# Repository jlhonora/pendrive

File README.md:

Build your own pendrive
=======================

This repo contains all the necessary material to build your own open-source pendrive, including the software source code, the design files and Gerber prints for the Printed Circuit Board and the 3D model of the plastic enclosure. Feel free to modify it as you like!

The microcontroller used is a TI msp430 of the F55xx family (msp430F5510 for now).

To use this library you need to [install mspgcc](https://github.com/jlhonora/mspgcc-install) and the __rake__ utility.

*WARNING*: The available code has only been tested on the [msp-exp430f5529](http://www.ti.com/tool/msp-exp430f5529) board. The PCB files are only an initial draft, and not a single one has been produced/tested.

## Motivation and principles ##

Technological devices that we use nowadays seem to be very far off from what someone could assemble at home. With this project we try to take down that myth, bringing technology and it's manufacturing process closer to normal people. 

The principles on which this project is built are the following:

- Open source code and designs
- Relatively easy soldering/assembly
- Expandable memory
- Small footprint/dimension

## Building the source code ##

First, build the source code:

    $ rake

And install it:

    $ sudo mspdebug rf2500 "prog bin.elf"

## References ##

The code here is heavily based on TI's msp-exp430F5529 User Experience Source Code, released under a BSD license.

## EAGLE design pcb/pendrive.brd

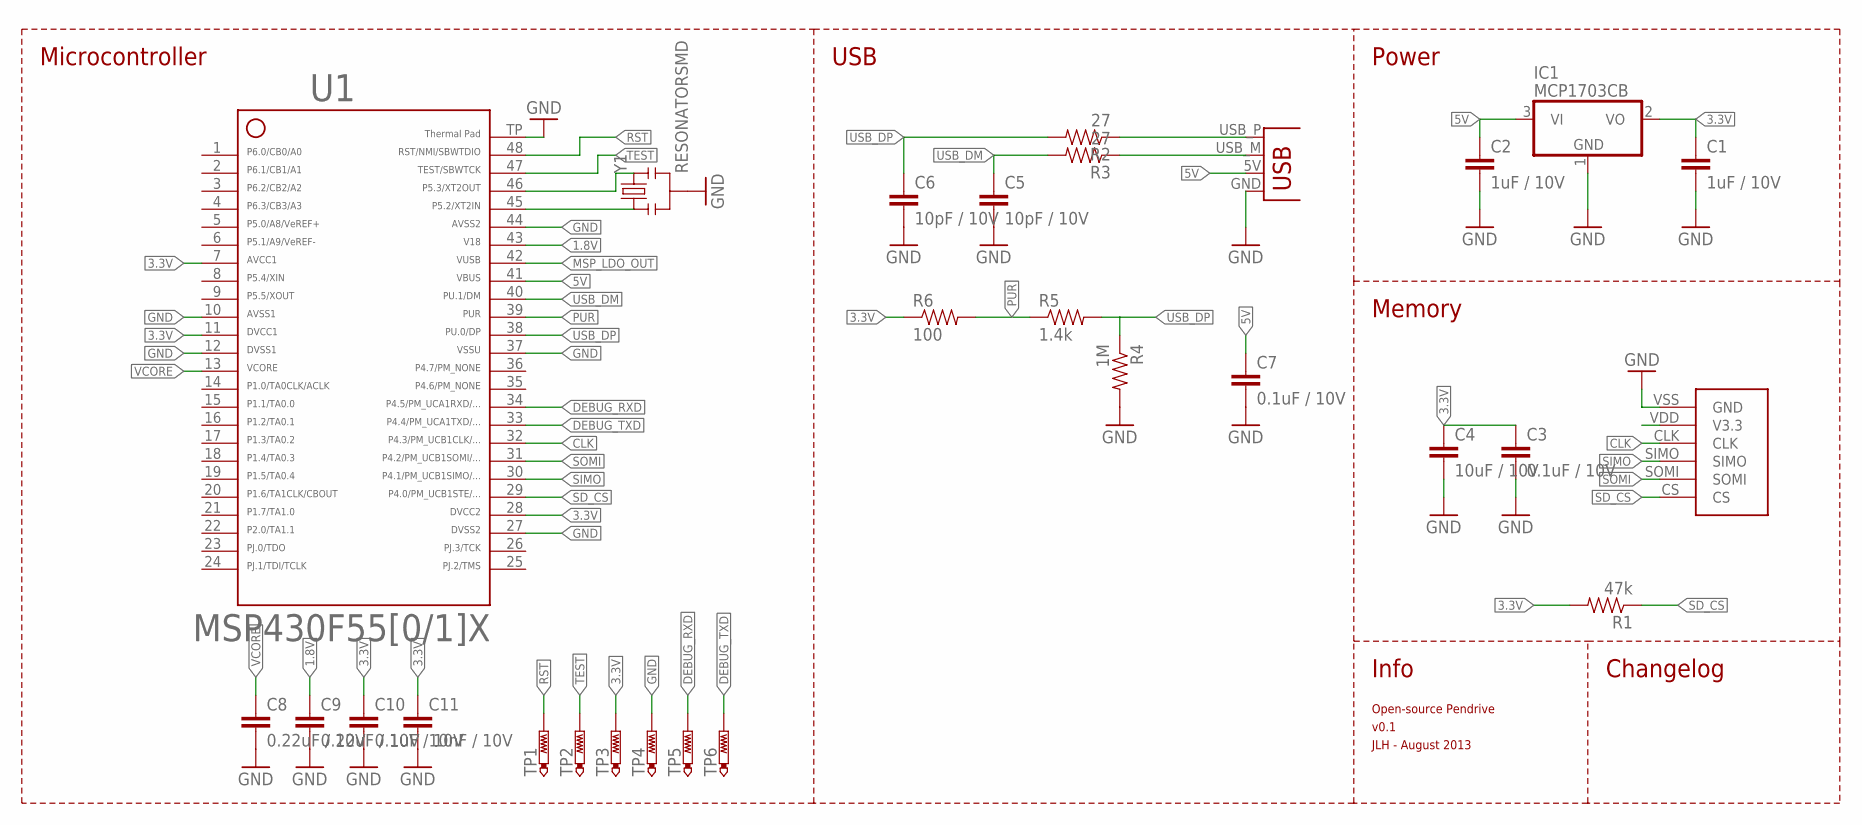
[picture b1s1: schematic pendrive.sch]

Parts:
C1, C2: 1uF / 10V; 0402-CAP
C3, C7, C10: 0.1uF / 10V; 0402-CAP
C4: 10uF / 10V; 1206
C5, C6: 10pF / 10V; 0402-CAP
C8, C9: 0.22uF / 10V; 0402-CAP
C11: 10nF / 10V; 0402-CAP
IC1: MCP1703CB; SOT23
R1: 47k; 0402-RES
R2, R3: 27; 0402-RES
R4: 1M; 0402-RES
R5: 1.4k; 0402-RES
R6: 100; 0402-RES
TP1, TP2, TP3, TP4, TP5, TP6: PTR1TP10SQ; TP10SQ
U1: F55[0/1]X---RGZ48; RGZ48
U2: MICROSD-MOLEX
X1: USBPCB; USB-A-PCB
Y1: RESONATORSMD; RESONATOR-SMD

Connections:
1.8V: C9.1, U1.43
3.3V: C1.1, C3.1, C4.1, C10.1, C11.1, IC1.2 (VO), R1.2, R6.1, TP3.TP, U1.7, U1.11, U1.28, U2.VDD (V3.3)
5V: C2.1, C7.1, IC1.3 (VI), U1.41, X1.5V (VBUS)
CLK: U1.32, U2.CLK
DEBUG_RXD: TP5.TP, U1.34
DEBUG_TXD: TP6.TP, U1.33
GND: C1.2, C2.2, C3.2, C4.2, C5.2, C6.2, C7.2, C8.2, C9.2, C10.2, C11.2, IC1.1 (GND), R4.2, TP4.TP, U1.10, U1.12, U1.27, U1.37, U1.44, U1.TP (49), U2.VSS (GND), X1.GND, Y1.2
MSP_LDO_OUT: U1.42
unnamed: R2.1, X1.USB_P (D+)
unnamed: R3.1, X1.USB_M (D-)
unnamed: U1.45, Y1.1
unnamed: U1.46, Y1.3
PUR: R5.1, R6.2, U1.39
RST: TP1.TP, U1.48
SD_CS: R1.1, U1.29, U2.CS
SIMO: U1.30, U2.SIMO
SOMI: U1.31, U2.SOMI
TEST: TP2.TP, U1.47
USB_DM: C5.1, R3.2, U1.40
USB_DP: C6.1, R2.2, R4.1, R5.2, U1.38
VCORE: C8.1, U1.13

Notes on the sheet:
Open-source Pendrive
v0.1
JLH - August 2013
Microcontroller
Power
Memory
Info
Changelog
USB

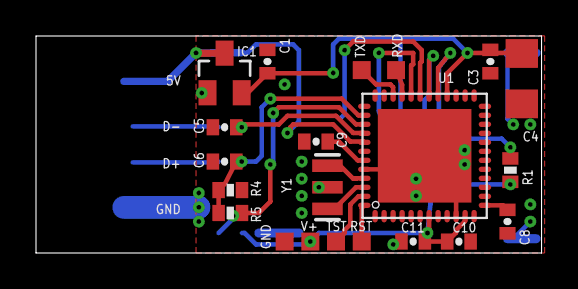
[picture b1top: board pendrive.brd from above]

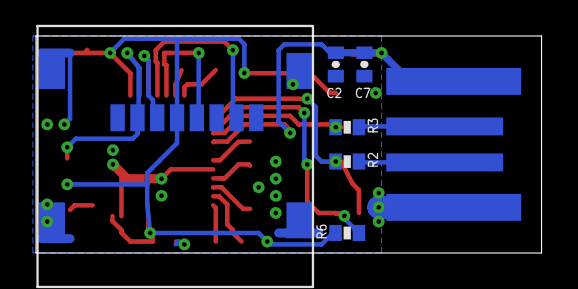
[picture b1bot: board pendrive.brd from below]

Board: 2 copper layers, 28.1 x 12.1 mm, 28 parts (7 on the bottom side), 20 nets.

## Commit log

2013-08-01 Initial commit, included cleanup
2013-08-01 Reorg
2013-08-01 Added schematic, board not routed yet
2013-08-01 Ignoring autosave files from Eagle
2013-08-01 First layout of components, not routed yet
2013-08-02 Added first routed PCB version, not tested yet
2013-08-02 Ignoring more autosave files from Eagle
2013-08-02 Added programming and test points
2013-08-02 Added small footprint as a goal
2013-08-02 Shrinked the board a little bit
2013-08-02 Added labels to test points and components
2013-08-02 Did a DRC, corrected a few things
2013-08-02 Small modification
2013-08-02 Changed a couple of things towards 5510 compilation

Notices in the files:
parts and their libraries:
SparkFun: Licensing: CC v3.0 Share-Alike You are welcome to use this library for commercial purposes.
